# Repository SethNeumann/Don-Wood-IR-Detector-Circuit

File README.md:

# REPO NAME: MRCS-Don-Wood-IR-Detector-Circuit

## License: Creative Commons Attribution-NonCommercial-ShareAlike

Don Wood offerd this circuit for an optical detector based on an IR emmitter/detector pair and
it used a segment of Dr. Chubb's SMC-12 as a substrate.  This is the same circuit without the
extraneous bits and and with dedicated pads for the pot and for a limiting resistor for the
emitter.  Terminal names stay close to the originals.  This ***may*** be a cost effective or
easier option for those needing a small number of detectors.  It will work as an ambient light
detector without an emitter but you are responsible for controlling ambient light and ensuring
illumination is consistent.

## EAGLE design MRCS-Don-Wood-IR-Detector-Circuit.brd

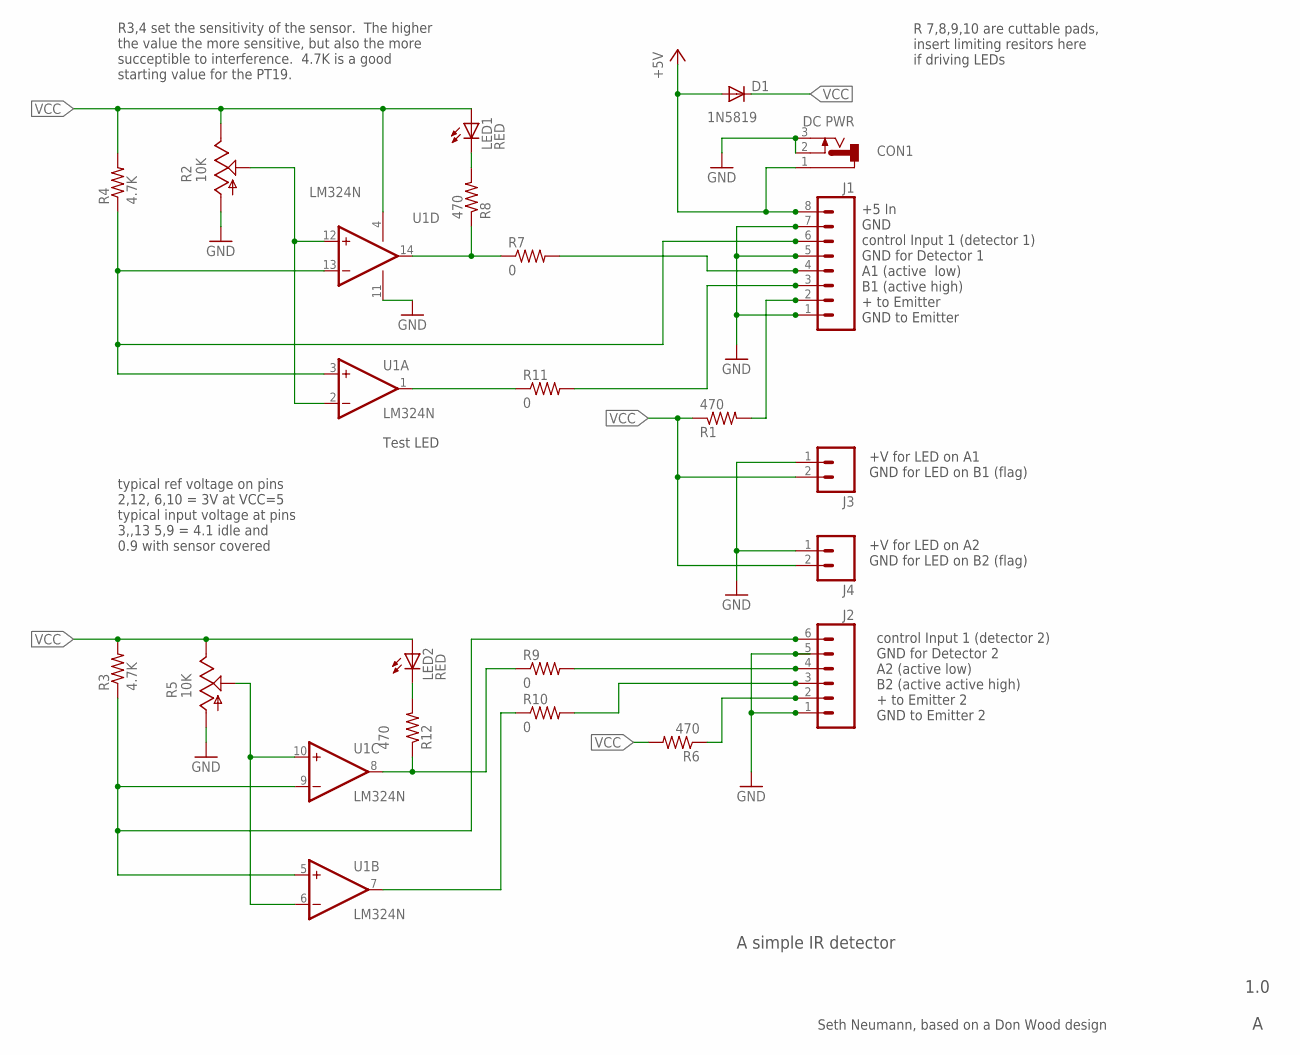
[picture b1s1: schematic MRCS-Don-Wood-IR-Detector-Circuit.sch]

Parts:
CON1: DC PWR; DCJ0202
D1: 1N5819; DIODE-1N4001
J1: CONNECTOR-M08LOCK; 1X08_LOCK
J2: CONNECTOR-M06LOCK; 1X06_LOCK
J3, J4: CONNECTOR-M021X02-LOCK; 1X02_LOCK
LED1, LED2: RED; LED3MM
R1, R6, R8, R12: 470; AXIAL-0.4-RES
R2, R5: 10K; RS3
R3, R4: 4.7K; AXIAL-0.4-RES
R7, R9, R10, R11: 0; CUT-R
U1: LM324N; DIL14

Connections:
+5V: CON1.1, D1.A, J1.8
A1: J1.4, R7.P1 (2)
A2: J2.4, R9.P1 (2)
B1: J1.3, R11.P1 (2)
B2: J2.3, R10.P1 (2)
GND: CON1.2, CON1.3, J1.1, J1.5, J1.7, J2.1, J2.5, J3.1 (A), J4.1 (A), R2.A, R5.A, U1.11 (V-)
IN1: J1.6, R4.P$1 (1), U1.3 (+IN), U1.13 (-IN)
IN2: J2.6, R3.P$1 (1), U1.5 (+IN), U1.9 (-IN)
unnamed: LED2.K (C), R12.P$2 (2)
unnamed: J1.2, R1.P$2 (2)
unnamed: R7.P2 (1), R8.P$1 (1), U1.14 (OUT)
unnamed: R9.P2 (1), R12.P$1 (1), U1.8 (OUT)
unnamed: R10.P2 (1), U1.7 (OUT)
unnamed: J2.2, R6.P$1 (1)
unnamed: R11.P2 (1), U1.1 (OUT)
unnamed: LED1.K (C), R8.P$2 (2)
REF1: R2.S, U1.2 (-IN), U1.12 (+IN)
REF2: R5.S, U1.6 (-IN), U1.10 (+IN)
VCC: D1.C, J3.2 (B), J4.2 (B), LED1.A, LED2.A, R1.P$1 (1), R2.E, R3.P$2 (2), R4.P$2 (2), R5.E, R6.P$2 (2), U1.4 (V+)

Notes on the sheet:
A simple IR detector
1.0
Seth Neumann, based on a Don Wood design
+5 In GND control Input 1 (detector 1) GND for Detector 1 A1 (active low) B1 (active high) + to Emitter GND to Emitter
control Input 1 (detector 2) GND for Detector 2 A2 (active low) B2 (active active high) + to Emitter 2 GND to Emitter 2
R 7,8,9,10 are cuttable pads, insert limiting resitors here if driving LEDs
+V for LED on A1 GND for LED on B1 (flag)
+V for LED on A2 GND for LED on B2 (flag)
typical ref voltage on pins 2,12, 6,10 = 3V at VCC=5 typical input voltage at pins 3,,13 5,9 = 4.1 idle and 0.9 with sensor covered
Test LED
R3,4 set the sensitivity of the sensor. The higher the value the more sensitive, but also the more succeptible to interference. 4.7K is a good starting value for the PT19.

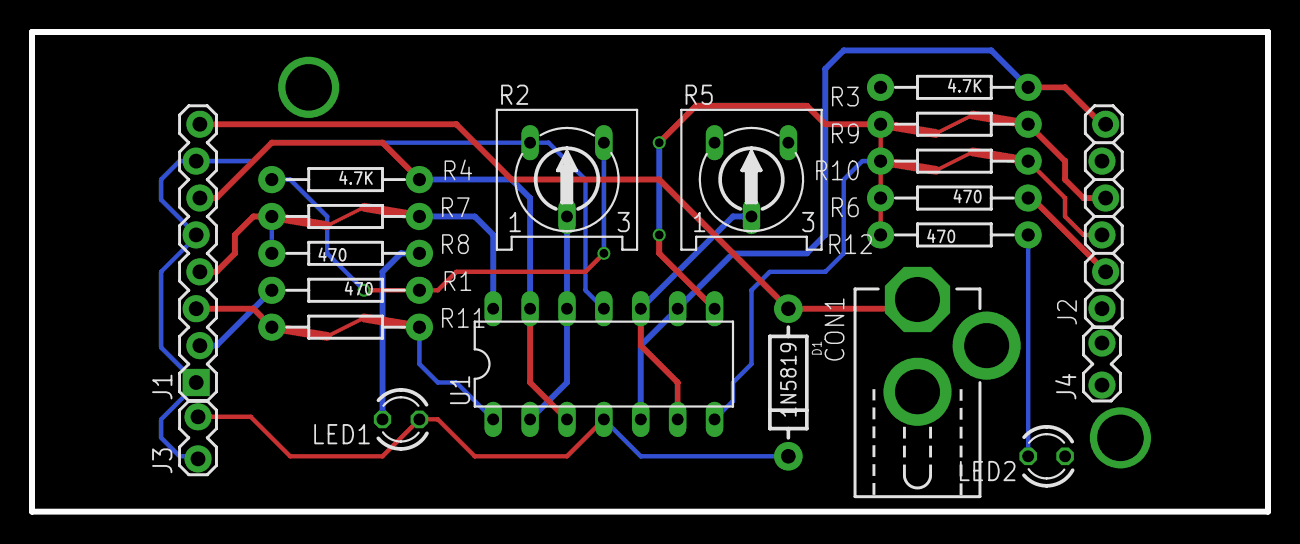
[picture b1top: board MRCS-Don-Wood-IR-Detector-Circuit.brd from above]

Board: 2 copper layers, 85.1 x 33.0 mm, 24 parts (0 on the bottom side), 19 nets.

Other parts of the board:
U$1: MRCSLOGOBTM
U$2: MRCSLOGOTOP
U$3: CA-PROP65WARNING

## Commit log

2020-10-02 Update INFO
2020-10-05 changes to connectors, added protection diode
    rearranged connectors so minimal system parts together, added
    protection diode
2020-10-29 first board sent to JLC
    first board
2020-11-24 moved the status LED to show illumination present
    The LED now lights when the the illumination is present. This is to help calibrate detection when using InfraRed illumination and reflected light set ups.
2020-12-20 misc work files
    should not show up
2020-12-24 Minor label changes, added work files to gitignore
    Changed the extra power and ground pads to "+5" and "GND" rather than LED+ and LED-. They can also be used for daisy chaining power and still can beused to power LEDs.
